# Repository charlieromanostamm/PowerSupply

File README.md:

# PowerSupply
This is the repo for the optoelectronic power supply designs

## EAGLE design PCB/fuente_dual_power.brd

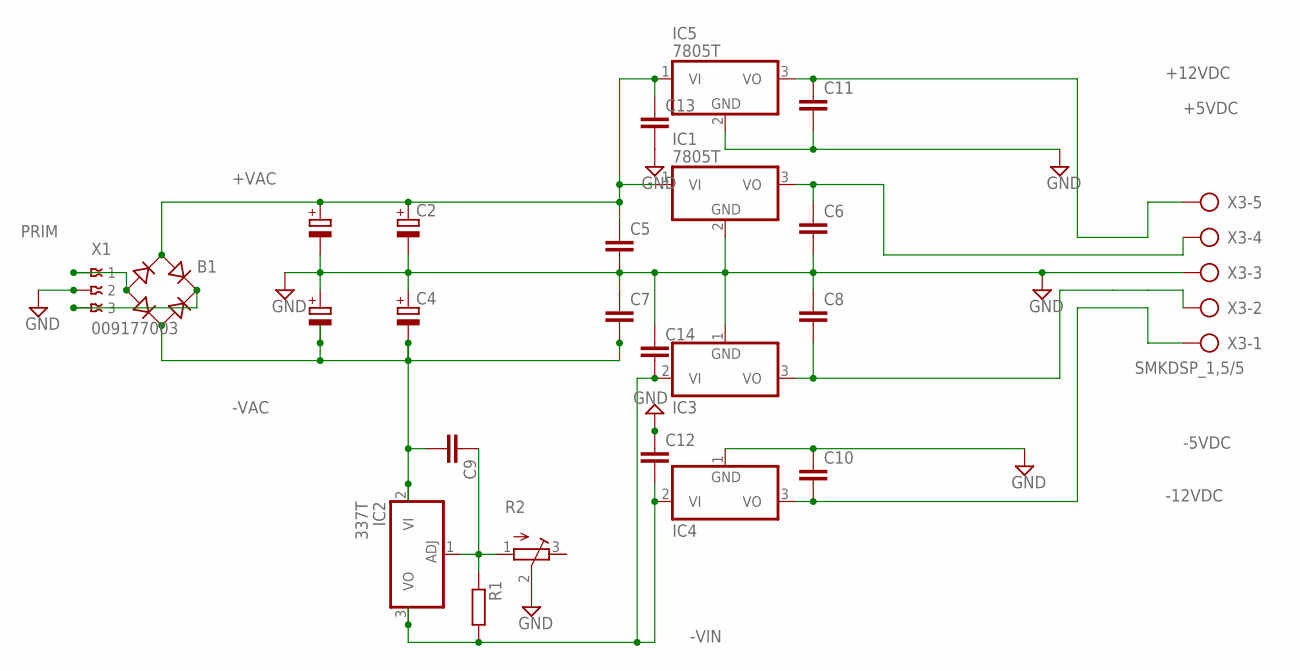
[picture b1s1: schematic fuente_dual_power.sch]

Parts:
B1: RB1A
C2, C4: CPOL-EUE1.8-4; E1,8-4
C5, C6, C7, C8, C9, C10, C11, C12, C13, C14: C5/7.2; C5B7.2
IC1, IC5: 7805T; TO220H
IC2: 337T; TO220H
IC3, IC4: 7905T; TO220H
R1: R-EU_0204/5; 0204/5
R2: R-TRIMM64W; RTRIM64W
X1: 009177003
X3: SMKDSP_1,5/5

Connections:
+5VDC: C6.1, IC1.3 (VO), X3.4
+12VDC: C11.1, IC5.3 (VO), X3.5
+VAC: B1.AC1, C2.+, C5.1, C13.1, IC1.1 (VI), IC5.1 (VI)
-5VDC: C8.2, IC3.3 (VO), X3.2
-12VDC: C10.2, IC4.3 (VO), X3.1
-VAC: B1.AC2, C4.-, C7.2, C9.2, IC2.2 (VI)
-VIN: C12.2, C14.2, IC2.3 (VO), IC3.2 (VI), IC4.2 (VI), R1.2
ADJ: C9.1, IC2.1 (ADJ), R1.1, R2.1 (A)
GND: C2.-, C4.+, C5.2, C6.2, C7.1, C8.1, C10.1, C11.2, C12.1, C13.2, C14.1, IC1.2 (GND), IC3.1 (GND), IC4.1 (GND), IC5.2 (GND), R2.2 (S), X1.2, X3.3
PRIM: B1.-, X1.1
SEC: B1.+, X1.3

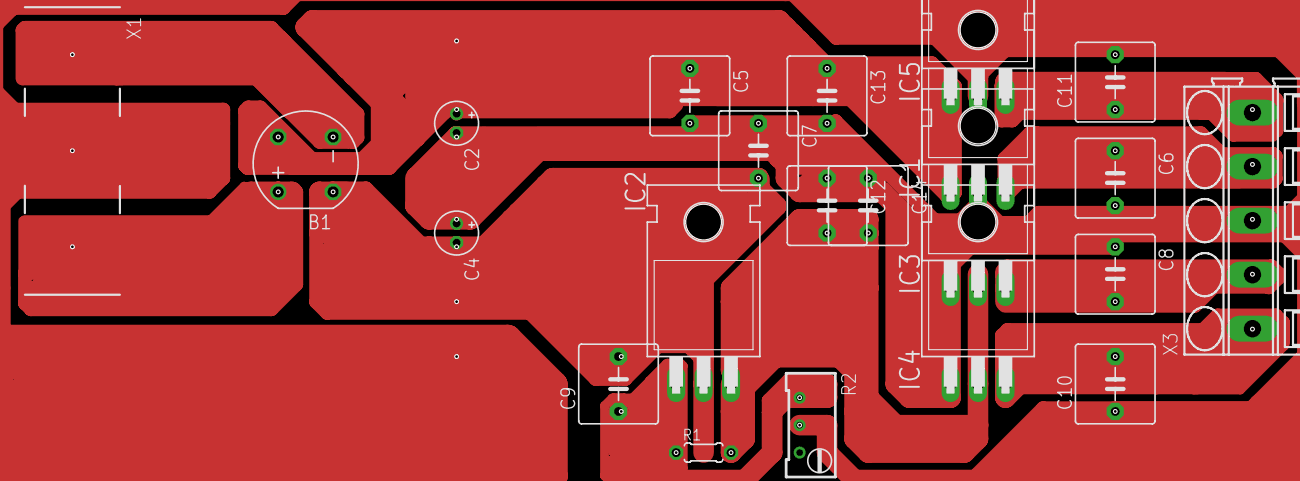
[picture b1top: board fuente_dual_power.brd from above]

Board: 2 copper layers, 22 parts (0 on the bottom side), 11 nets.

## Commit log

2021-07-29 include FIUBA designs
